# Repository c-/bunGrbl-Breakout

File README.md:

# bunGrbl-Breakout

This is a Kicad breakout board for an older Bungard CCD (ATC in this case,
but it should work with manual change spindles) PCB mill. That's the
version with the DB-25 and male/female DB-15's. It's intended to be used
with a [GRBL](https://github.com/gnea/grbl/wiki) controller of some sort.

At the moment I'm running my machine with a custom ATMega328P GRBL
controller (Uno/Nano equivalent), DM542 stepper drivers, a JYQD-V8.5E bldc
motor driver, and a Meanwell LRS 350-24 PSU. The spindle maxes out around
35k RPM with that motor driver, but otherwise everything works fine.

To release the pneumatic collet, the CHUCK signal should be pulled to GND
by a switch.

X,Y,Z limit switches are wired NC. The tool length switch (TOOL) is NO, and
I've split that off on my machine into a connector for performing the usual
auto-leveling.

I've milled my board single sided as there's only a couple of jumpers
needed.

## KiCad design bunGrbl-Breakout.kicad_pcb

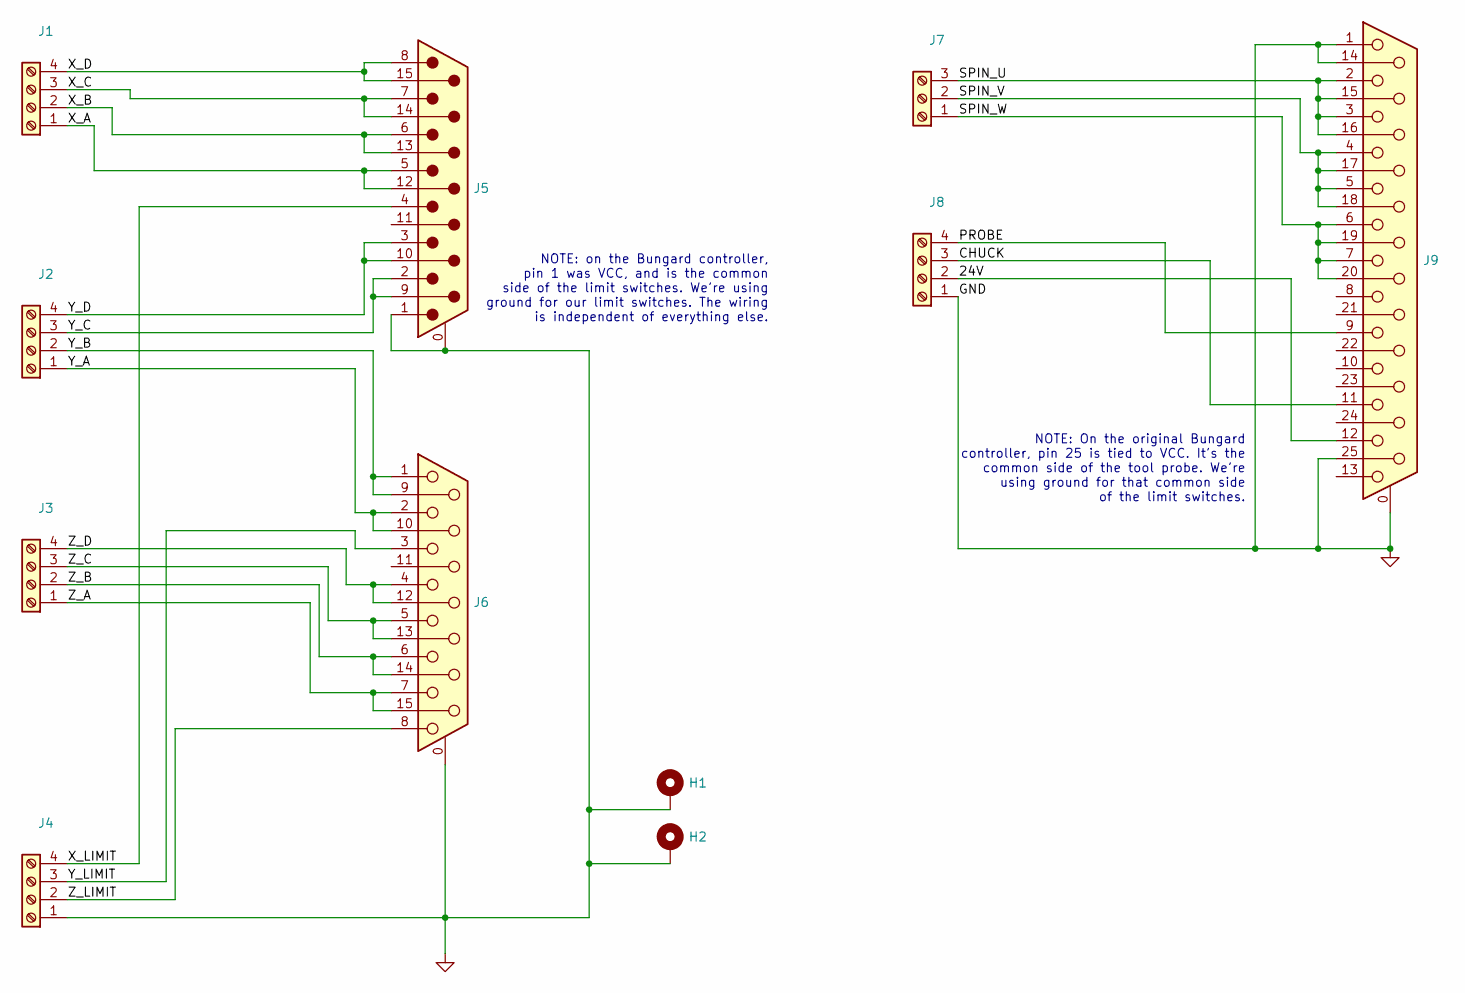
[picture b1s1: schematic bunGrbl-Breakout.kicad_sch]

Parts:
H1, H2: MountingHole_5.3mm_M5_Pad
J1, J2, J3, J4, J8: TerminalBlock_MetzConnect_Type086_RT03404HBLC_1x04_P3.81mm_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
J5: DSUB-15_Male_Horizontal_FatPin_P2.77x2.84mm_EdgePinOffset7.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
J6: DSUB-15_Female_Horizontal_FatPin_P2.77x2.84mm_EdgePinOffset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
J7: TerminalBlock_Phoenix_MKDS-3-3-5.08_1x03_P5.08mm_Horizontal
J9: DSUB-25_Female_Horizontal_FatPad_P2.77x2.84mm_EdgePinOffset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

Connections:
/24V: J8.2, J9.12
/CHUCK: J8.3, J9.11
/PROBE: J8.4, J9.9
/SPIN_U: J7.3, J9.2, J9.3, J9.15, J9.16
/SPIN_V: J7.2, J9.4, J9.5, J9.17, J9.18
/SPIN_W: J7.1, J9.6, J9.7, J9.19, J9.20
/X_A: J1.1, J5.5, J5.12
/X_B: J1.2, J5.6, J5.13
/X_C: J1.3, J5.7, J5.14
/X_D: J1.4, J5.8, J5.15
/X_LIMIT: J4.4, J5.4
/Y_A: J2.1, J6.2, J6.10
/Y_B: J2.2, J6.1, J6.9
/Y_C: J2.3, J5.2, J5.9
/Y_D: J2.4, J5.3, J5.10
/Y_LIMIT: J4.3, J6.3
/Z_A: J3.1, J6.7, J6.15
/Z_B: J3.2, J6.6, J6.14
/Z_C: J3.3, J6.5, J6.13
/Z_D: J3.4, J6.4, J6.12
/Z_LIMIT: J4.2, J6.8
GND: H1.1, H2.1, J4.1, J5.0 (PAD), J5.1, J6.0 (PAD), J8.1, J9.0 (PAD), J9.1, J9.14, J9.25

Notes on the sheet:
NOTE: On the original Bungard controller, pin 25 is tied to VCC. It's the common side of the tool probe. We're using ground for that common side of the limit switches.
NOTE: on the Bungard controller, pin 1 was VCC, and is the common side of the limit switches. We're using ground for our limit switches. The wiring is independent of everything else.

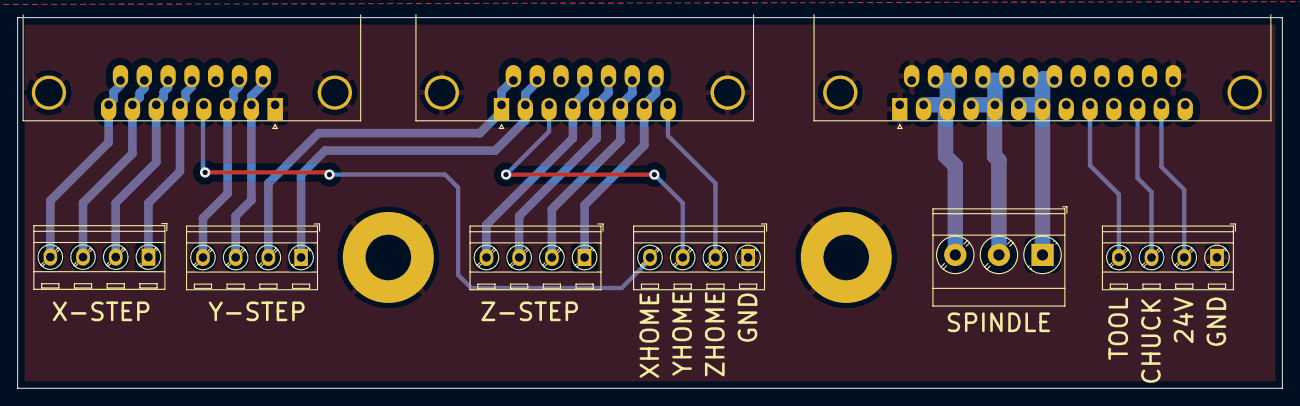
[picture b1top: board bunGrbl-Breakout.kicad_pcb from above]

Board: 2 copper layers, 147.3 x 43.2 mm, 11 parts (0 on the bottom side), 22 nets.

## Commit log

2022-12-09 initial import
2022-12-09 fix link
2022-12-09 trivial doc fixes
